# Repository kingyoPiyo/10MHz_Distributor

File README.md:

# 10MHz_Distributor
GPSDOなどの10MHz基準信号の分配基板です。  
出力部に5段のBPFを搭載しており、入力信号をバッファリング＆正弦波へ波形整形してから出力します。 

# 諸特性
・・・部品到着、組み立て後に詳細測定予定・・・  

|  項目  |  仕様 |  備考  |
| ---------- | ------ | ------------- |
|  電源電圧  |  9 ～ 15 V  | NJM7805耐圧は35V |
|  消費電流  |  約 xx mA  | 電源電圧12V, 4出力50Ω終端時 |
|  入力インピーダンス  |  約 xxx Ω  | R19にて50Ω終端可 |
|  入力信号レベル  |  xx ～ xx Vp-p  |  |
|  出力インピーダンス  |  50 Ω  |  |
|  出力信号レベル  |  xx ～ xx dBm  | 50Ω終端時 |
|  スプリアスレベル  |  < -xx dBm (2nd)<br>< -xx dBm (3rd)<br>< -xx dBm (4th)  | 50Ω終端時 |
|  SSB位相雑音  |  -xx dBc/Hz 10kHz offset<br>-xx dBc/Hz 30kHz offset<br>-xx dBc/Hz 100kHz offset  | 50Ω終端時<br>入力信号はxxx |

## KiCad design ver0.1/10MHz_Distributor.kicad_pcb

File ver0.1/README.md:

# 10MHz_Distributor(ver 0.1)
GPSDOなどの10MHz基準信号の分配基板です。  
出力部に5段のBPFを搭載しており、入力信号をバッファリング＆正弦波へ波形整形してから出力します。 

# 諸特性
インダクタのQ値が考慮できておらず、通過帯域での減衰量が非常に大きくなりました。  
インダクタを変更して再設計します。（続く・・・）  
* インダクタ：LQW18ANR47J00  
* Q値：5.5@10MHz  
* DCR：5.3Ω@10MHz

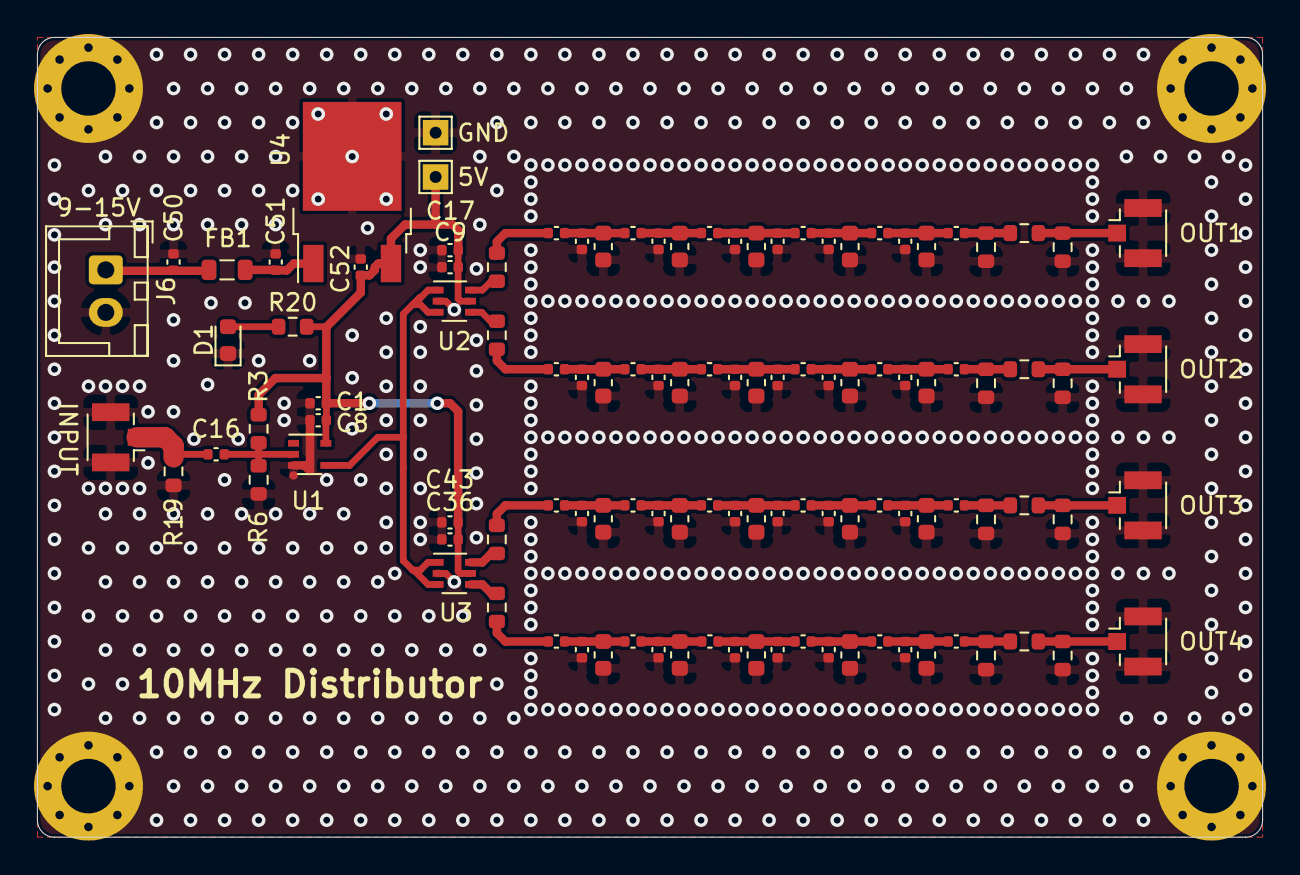
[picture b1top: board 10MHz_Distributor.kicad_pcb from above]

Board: 2 copper layers, 72.0 x 47.0 mm, 116 parts (0 on the bottom side), 44 nets.

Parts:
C1, C9, C36, C50, C51: 1u; C_0402_1005Metric
C2, C7, C18, C23, C30, C35, C44, C49: GCM1555C1H221FA16D; C_0402_1005Metric
C3, C6, C19, C22, C31, C34, C45, C48: GRM1555C1H910JA01D; C_0402_1005Metric
C4, C5, C20, C21, C32, C33, C46, C47: GRM1555C1H680JA01D; C_0402_1005Metric
C8, C16, C17, C43, C52: 0.1u; C_0402_1005Metric
C10, C15, C24, C29, C37, C42, C53, C58: GRM1555C1H331FA01D; C_0402_1005Metric
C11, C13, C14, C25, C27, C28, C38, C40, C41, C54, C56, C57: GRM1555C1H391FA01D; C_0402_1005Metric
C12, C26, C39, C55: GRM1555C1H300GA01D; C_0402_1005Metric
D1: LED; LED_0603_1608Metric
FB1: BLM21PG331SN; L_0805_2012Metric
H1, H2, H3, H4: MountingHole_Pad; MountingHole_3.2mm_M3_Pad_Via
J1, J3, J4, J5: OUT1; U.FL_Hirose_U.FL-R-SMT-1_Vertical
J2: IN; U.FL_Hirose_U.FL-R-SMT-1_Vertical
J6: POWER_INPUT; JST_XH_B2B-XH-A_1x02_P2.50mm_Vertical
L1, L2, L3, L4, L5, L6, L7, L8, L9, L10, L11, L12, L13, L14, L15, L16, L17, L18, L19, L20: LQW18ANR47J00D; L_0603_1608Metric
R1, R7, R11, R15: 47R; R_0603_1608Metric
R2, R8, R12, R16: 17R6; R_0603_1608Metric
R3, R6, R20: 1k; R_0603_1608Metric
R4, R5, R9, R10, R13, R14, R17, R18: 292R4; R_0603_1608Metric
R19: NM; R_0603_1608Metric
TP1: 5V; TestPoint_THTPad_1.5x1.5mm_Drill0.7mm
TP2: GND; TestPoint_THTPad_1.5x1.5mm_Drill0.7mm
U1: TC7S14F / NC7SZ14P5XCT-ND; SOT-353_SC-70-5
U2, U3: NLV27WZ16DFT2G; SOT-363_SC-70-6
U4: NJM7805SDL1; TO-252-2

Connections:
+5V: C1.2, C8.2, C9.2, C17.2, C36.2, C43.2, C52.2, R3.1, R20.2, TP1.1, U1.5, U2.5, U3.5, U4.3
GND: C1.1, C8.1, C9.1, C10.2, C11.2, C12.2, C13.2, C14.2, C15.2, C17.1, C24.2, C25.2, C26.2, C27.2, C28.2, C29.2, C36.1, C37.2, C38.2, C39.2, C40.2, C41.2, C42.2, C43.1, C50.1, C51.1, C52.1, C53.2, C54.2, C55.2, C56.2, C57.2, C58.2, D1.1, H1.1, H2.1, H3.1, H4.1, J1.2, J2.2, J3.2, J4.2, J5.2, J6.2, L1.2, L2.2, L3.2, L4.2, L5.2, L6.2, L7.2, L8.2, L9.2, L10.2, L11.2, L12.2, L13.2, L14.2, L15.2, L16.2, L17.2, L18.2, L19.2, L20.2, R4.2, R5.2, R6.2, R9.2, R10.2, R13.2, R14.2, R17.2, R18.2, R19.2, TP2.1, U1.3, U2.2, U3.2, U4.2
unnamed: C2.2, R1.1
unnamed: C7.1, R2.2, R4.1
unnamed: C2.1, C3.2, C10.1, L1.1
unnamed: C3.1, C4.2, C11.1, L2.1
unnamed: C4.1, C5.2, C12.1, C13.1, L3.1
unnamed: C5.1, C6.2, C14.1, L4.1
unnamed: C6.1, C7.2, C15.1, L5.1
unnamed: C16.1, R3.2, R6.1, U1.2
unnamed: C16.2, J2.1, R19.1
unnamed: C18.1, C19.2, C24.1, L6.1
unnamed: C18.2, R7.1
unnamed: C19.1, C20.2, C25.1, L7.1
unnamed: C20.1, C21.2, C26.1, C27.1, L8.1
unnamed: C21.1, C22.2, C28.1, L9.1
unnamed: C22.1, C23.2, C29.1, L10.1
unnamed: C23.1, R8.2, R9.1
unnamed: C30.1, C31.2, C37.1, L11.1
unnamed: C30.2, R11.1
unnamed: C31.1, C32.2, C38.1, L12.1
unnamed: C32.1, C33.2, C39.1, C40.1, L13.1
unnamed: C33.1, C34.2, C41.1, L14.1
unnamed: C34.1, C35.2, C42.1, L15.1
unnamed: C35.1, R12.2, R13.1
unnamed: C44.1, C45.2, C53.1, L16.1
unnamed: C44.2, R15.1
unnamed: C45.1, C46.2, C54.1, L17.1
unnamed: C46.1, C47.2, C55.1, C56.1, L18.1
unnamed: C47.1, C48.2, C57.1, L19.1
unnamed: C48.1, C49.2, C58.1, L20.1
unnamed: C49.1, R16.2, R17.1
unnamed: C50.2, FB1.2, J6.1
unnamed: C51.2, FB1.1, U4.1
unnamed: D1.2, R20.1
unnamed: J1.1, R2.1, R5.1
unnamed: J3.1, R8.1, R10.1
unnamed: J4.1, R12.1, R14.1
unnamed: J5.1, R16.1, R18.1
unnamed: R1.2, U2.6
unnamed: R7.2, U2.4
unnamed: R11.2, U3.6
unnamed: R15.2, U3.4
unnamed: U1.4, U2.1, U2.3, U3.1, U3.3

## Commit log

2021-06-12 Add some files
2021-06-26 Fix inductor values
2021-06-26 Q値反映
2021-06-26 フォルダ移動
2021-06-26 S21差し替え
